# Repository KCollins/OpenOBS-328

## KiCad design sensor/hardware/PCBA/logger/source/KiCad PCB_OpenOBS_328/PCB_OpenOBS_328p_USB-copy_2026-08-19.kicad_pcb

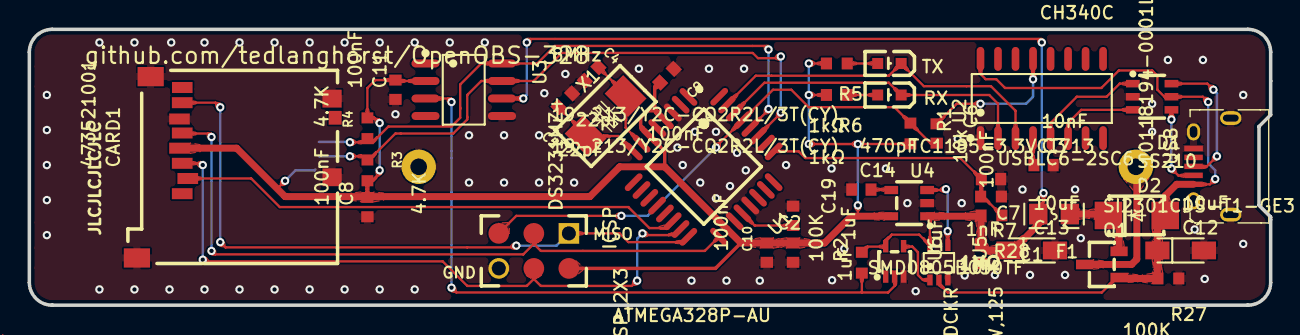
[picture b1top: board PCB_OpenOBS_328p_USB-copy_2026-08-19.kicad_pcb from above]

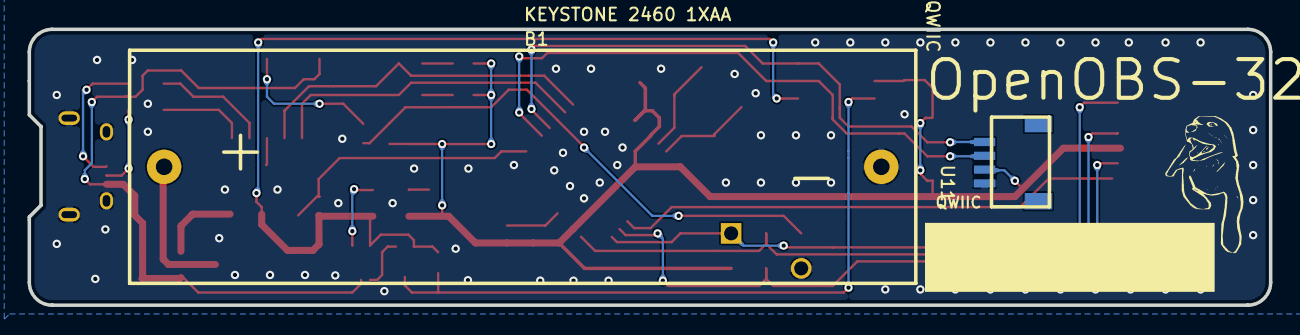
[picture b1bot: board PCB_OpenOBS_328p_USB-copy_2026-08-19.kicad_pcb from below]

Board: 2 copper layers, 90.0 x 20.0 mm, 42 parts (2 on the bottom side), 31 nets.

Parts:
B1: KEYSTONE 2460 1XAA
C1, C2, C19: 1uF; C0603
C3: 10nF; C0603
C4, C5: 22pF; C0603
C6, C8, C9, C10, C11: 100nF; C0603
C7: 1nF; C0603
C12, C13: 10uF; CAP-SMD_L3.2-W1.6-R-RD
C14: 470pF; C0603
CARD1: 473521001; SD-SMD_SD-47352-101
D1: USBLC6-2SC6; SOT-23-6_L2.9-W1.6-P0.95-LS2.8-BR
D2: SS210; SMA_L4.3-W2.6-LS5.2-RD
F1: SMD0805B050TF; F0805
ICSP: ICSP_2X3; CON2X3
Q1: SI2301CDS-T1-GE3; SOT-23-3_L3.0-W1.7-P0.95-LS2.9-BR
R1: 10k; R0603
R2, R27: 100K; R0603
R3, R4: 4.7K; R0603
R5, R6: 1kΩ; R0603
R7: 1MΩ; R0603
R28: 10M; R0603
RX: 19-213/Y2C-CQ2R2L/3T(CY); LED0603-R-RD
TX: 19-213/Y2C-CQ2R2L/3T(CY); LED0603-R-RD
U1: ATMEGA328P-AU; TQFP-32_L7.0-W7.0-P0.80-LS9.0-BL
U2: CH340C; SOP-16_L10.0-W3.9-P1.27-LS6.0-BL
U3: DS3231MZ+; SOIC-8_L4.9-W3.9-P1.27-LS6.0-BL
U4: TC1185-3.3VCT713; SOT-23-5_L3.0-W1.7-P0.95-LS2.8-BR
U5: 74AHC1G32GW,125; SOT-353_L2.2-W1.4-P0.65-LS2.4-BR
U6: SN74LVC1G14DCKR; SC-70-5_L2.1-W1.3-P0.65-LS2.1-BR
U11: QWIIC; QWIIC CONNECTOR
USB: 10118194-0001LF; MICRO-USB-SMD_10118194-0001LF
X1: 8MHz; CRYSTAL-SMD_L5.0-W3.2

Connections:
C4_1: C4.1, U1.7, X1.2
C5_2: C5.2, U1.8, X1.1
C19_2: C19.2, U1.20
CS: CARD1.2, U1.14
GND: B1.2, C1.1, C2.2, C3.2, C4.2, C5.1, C7.1, C8.1, C9.1, C10.1, C11.1, C12.2, C13.2, C14.1, C19.1, CARD1.6, CARD1.EH, D1.2, ICSP.6, R7.1, R27.1, U1.3, U1.5, U1.21, U2.1, U3.5, U4.2, U5.3, U6.3, U11.1, USB.5, USB.6
MISO: CARD1.7, ICSP.1, U1.16
MOSI: CARD1.3, ICSP.4, U1.15
PINTERRUPT: R2.1, U3.3, U6.2
PRESET: C6.2, ICSP.5, R1.1, U1.29
Q1_2: D2.1, F1.1, Q1.2
R28_1: C7.2, R7.2, R28.1, U1.25
RX: RX.2, U1.30, U2.2
RX_1: R6.1, RX.1
SCK: CARD1.5, ICSP.3, U1.17
SCL: R4.1, U1.28, U3.8, U11.4
SDA: R3.1, U1.27, U3.7, U11.3
TX: TX.2, U1.31, U2.3
TX_1: R5.1, TX.1
U2_4: C3.1, U2.4
U2_5: D1.1, U2.5
U2_6: D1.3, U2.6
U2_13: C6.1, U2.13
U4_4: C14.2, U4.4
U5_1: U5.1, U6.4
U5_4: U4.3, U5.4
USB_2: D1.4, USB.2
USB_3: D1.6, USB.3
VBAT: B1.1, Q1.3
VCC: C2.1, C8.2, C9.2, C10.2, C11.2, CARD1.4, ICSP.2, R1.2, R3.2, R4.2, R5.2, R6.2, U1.4, U1.6, U1.18, U3.2, U4.5, U11.2
VIN: C1.2, C13.1, F1.2, R2.2, R28.2, U3.6, U4.1, U5.5, U6.5
VUSB: C12.1, D1.5, D2.2, Q1.1, R27.2, U2.16, U5.2, USB.1
